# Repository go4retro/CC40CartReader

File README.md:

# CC40CartReader
Arduino PCB and software to read TI cc40 cartridges

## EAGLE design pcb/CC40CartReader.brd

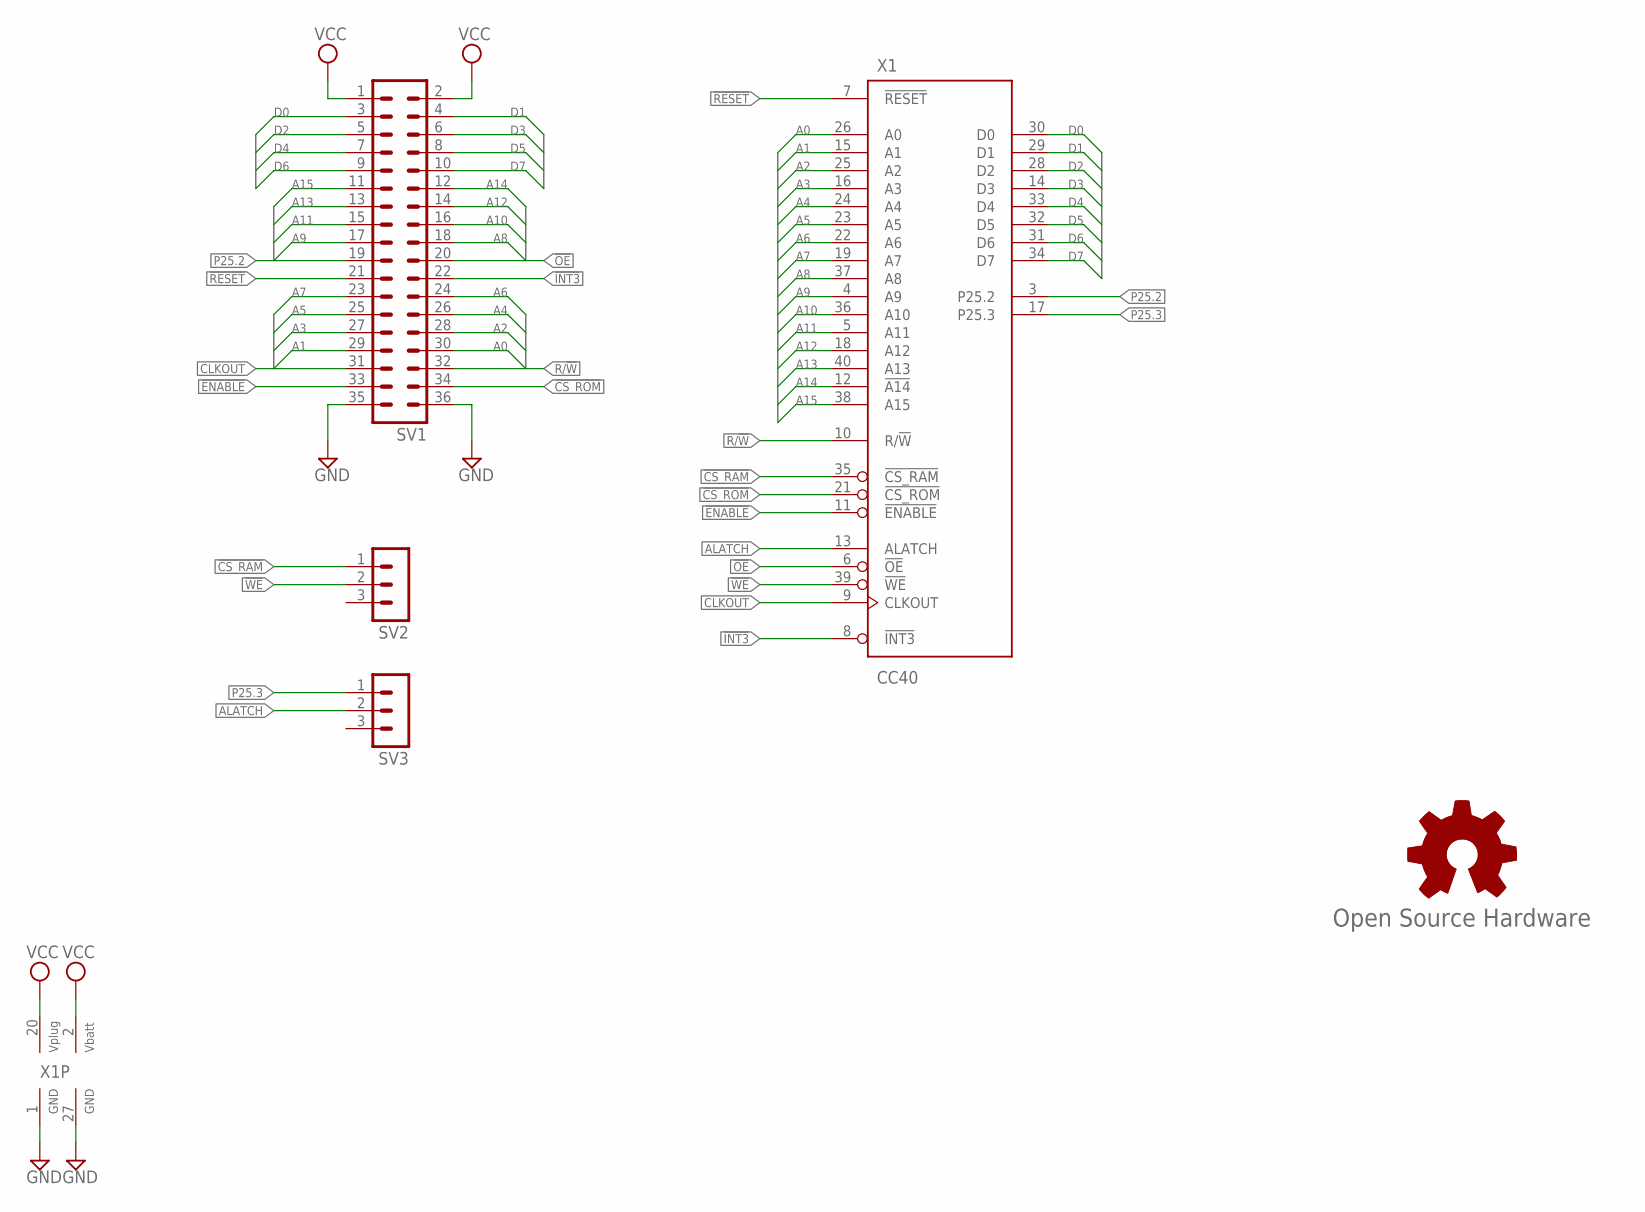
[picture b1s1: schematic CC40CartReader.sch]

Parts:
GOLD_ORB_SM1: Open Source Hardware; OSHW_8MM
SV1: MA18-2
SV2, SV3: MA03-1
X1: CC40; FE20-2(.050)SHORT

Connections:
!CS_RAM: SV2.1, X1.35 (!CS_RAM)
!CS_ROM: SV1.34, X1.21 (!CS_ROM)
!ENABLE: SV1.33, X1.11 (!ENABLE)
!INT3: SV1.22, X1.8 (!INT3)
!OE: SV1.20, X1.6 (!OE)
!RESET: SV1.21, X1.7 (!RESET)
!WE: SV2.2, X1.39 (!WE)
A0: SV1.30, X1.26 (A0)
A1: SV1.29, X1.15 (A1)
A2: SV1.28, X1.25 (A2)
A3: SV1.27, X1.16 (A3)
A4: SV1.26, X1.24 (A4)
A5: SV1.25, X1.23 (A5)
A6: SV1.24, X1.22 (A6)
A7: SV1.23, X1.19 (A7)
A8: SV1.18, X1.37 (A8)
A9: SV1.17, X1.4 (A9)
A10: SV1.16, X1.36 (A10)
A11: SV1.15, X1.5 (A11)
A12: SV1.14, X1.18 (A12)
A13: SV1.13, X1.40 (A13)
A14: SV1.12, X1.12 (!A14)
A15: SV1.11, X1.38 (A15)
ALATCH: SV3.2, X1.13 (ALATCH)
CLKOUT: SV1.31, X1.9 (CLKOUT)
D0: SV1.3, X1.30 (D0)
D1: SV1.4, X1.29 (D1)
D2: SV1.5, X1.28 (D2)
D3: SV1.6, X1.14 (D3)
D4: SV1.7, X1.33 (D4)
D5: SV1.8, X1.32 (D5)
D6: SV1.9, X1.31 (D6)
D7: SV1.10, X1.34 (D7)
GND: SV1.35, SV1.36, X1.1 (GND), X1.27 (GND)
P25.2: SV1.19, X1.3 (P25.2)
P25.3: SV3.1, X1.17 (P25.3)
R/!W: SV1.32, X1.10 (R/!W)
VCC: SV1.1, SV1.2, X1.2 (VBATT), X1.20 (VPLUG)

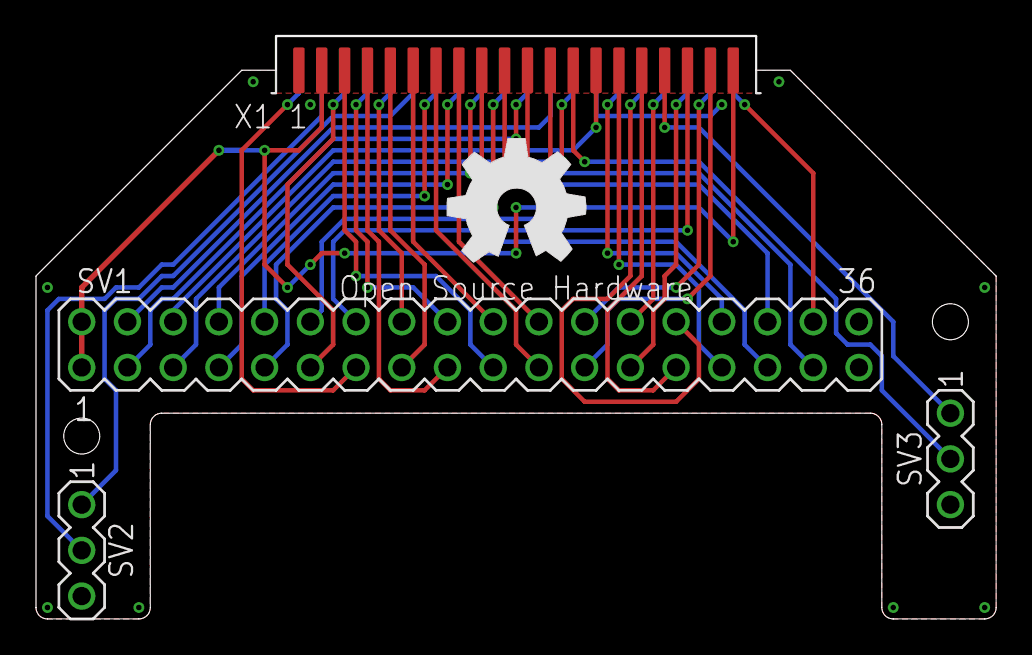
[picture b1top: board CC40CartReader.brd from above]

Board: 2 copper layers, 53.3 x 32.4 mm, 5 parts (0 on the bottom side), 38 nets.
